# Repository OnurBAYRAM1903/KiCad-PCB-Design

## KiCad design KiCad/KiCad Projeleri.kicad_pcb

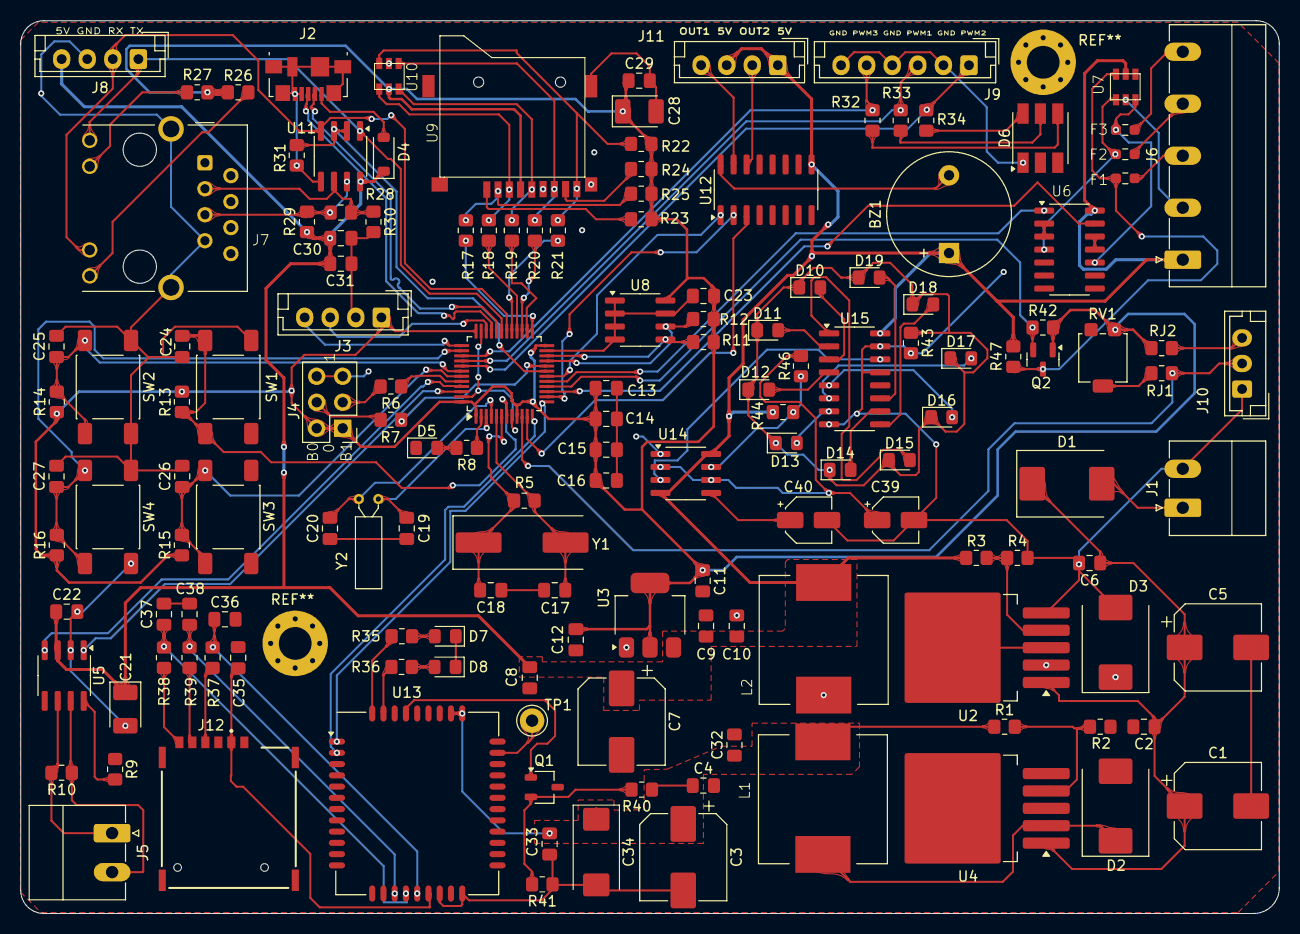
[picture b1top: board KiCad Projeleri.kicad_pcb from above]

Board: 2 copper layers, 123.0 x 87.2 mm, 149 parts (0 on the bottom side), 112 nets.

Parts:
BZ1: Buzzer; Buzzer_12x9.5RM7.6
C1, C5: 100uF-50V; CP_Elec_8x10
C2, C4, C6, C8, C10, C11, C13, C14, C15, C16, C22, C23, C24, C25, C26, C27, C30, C32, C33, C35: 100nF; C_0805_2012Metric_Pad1.18x1.45mm_HandSolder
C3, C7: 220uF-16V; CP_Elec_8x10
C9: 22uF; C_0805_2012Metric_Pad1.18x1.45mm_HandSolder
C12: 47uF; C_0805_2012Metric_Pad1.18x1.45mm_HandSolder
C17, C18, C19, C20: 22pF; C_0805_2012Metric_Pad1.18x1.45mm_HandSolder
C21: 47uF; CP_EIA-3528-21_Kemet-B_HandSolder
C28: 4.7uF-10V; CP_EIA-3528-21_Kemet-B_HandSolder
C29: 100nF-10V; C_0805_2012Metric_Pad1.18x1.45mm_HandSolder
C31: 10uF; C_0805_2012Metric_Pad1.18x1.45mm_HandSolder
C34: 100uF-10V; CP_EIA-7343-31_Kemet-D_HandSolder
C36, C37, C38: 33pF; C_0805_2012Metric_Pad1.18x1.45mm_HandSolder
C39: C_Polarized_Small; CP_Elec_4x5.4
C40: 1uF; CP_Elec_4x5.4
D1, D2, D3: SS34; D_SMC
D4: D_Schottky_Small; D_SOD-123
D5, D10, D11, D12, D13, D14, D15, D16, D17, D18, D19: LED_BLUE; LED_0805_2012Metric_Pad1.15x1.40mm_HandSolder
D6: LED_RGB; LED_RGB_5050-6
D7, D8: LED_ORANGE; LED_0805_2012Metric_Pad1.15x1.40mm_HandSolder
F1, F2, F3: RESETTABLE_FUSE-0603
J1: Conn_01x02; PhoenixContact_MC_1,5_2-G-3.81_1x02_P3.81mm_Horizontal
J2: USB_OTG; USB_Micro-B_Molex_47346-0001
J3, J8, J11: Conn_01x04; JST_EH_B4B-EH-A_1x04_P2.50mm_Vertical
J4: Conn_02x03_Counter_Clockwise; PinHeader_2x03_P2.54mm_Vertical
J5: Screw_Terminal_01x02; PhoenixContact_MC_1,5_2-G-3.81_1x02_P3.81mm_Horizontal
J6: Conn_01x05; PhoenixContact_MC_1,5_5-G-5.08_1x05_P5.08mm_Horizontal
J7: RJ45_USER
J9: Conn_01x06; JST_EH_B6B-EH-A_1x06_P2.50mm_Vertical
J10: Conn_01x03; JST_EH_B3B-EH-A_1x03_P2.50mm_Vertical
J12: SIM_Card-8066; GCT_SIM8066-6-1-14-01-A_REVA
L1, L2: 47uH; INDUCTOR_12x12x8
Q1: BC337; TSOT-23
Q2: BSS138; SOT-23
R1: 2K; R_0805_2012Metric_Pad1.20x1.40mm_HandSolder
R2, R4, R9, R26, R27, R28, R44, R46: 1K; R_0805_2012Metric_Pad1.20x1.40mm_HandSolder
R3: 3K; R_0805_2012Metric_Pad1.20x1.40mm_HandSolder
R5: 1M; R_0805_2012Metric_Pad1.20x1.40mm_HandSolder
R6, R7, R22, R31, R42, R47: 10K; R_0805_2012Metric_Pad1.20x1.40mm_HandSolder
R8, R33, R43: 330R; R_0805_2012Metric_Pad1.20x1.40mm_HandSolder
R10: 120R; R_0805_2012Metric_Pad1.20x1.40mm_HandSolder
R11, R12, R13, R14, R15, R16, R23, R24, R40, R41: 4K7; R_0805_2012Metric_Pad1.20x1.40mm_HandSolder
R17: 0R; R_0805_2012Metric_Pad1.20x1.40mm_HandSolder
R18, R19, R20, R37, R38, R39: 47R; R_0805_2012Metric_Pad1.20x1.40mm_HandSolder
R21: 1K8; R_0805_2012Metric_Pad1.20x1.40mm_HandSolder
R25: 47K; R_0805_2012Metric_Pad1.20x1.40mm_HandSolder
R29, R30: 20K; R_0805_2012Metric_Pad1.20x1.40mm_HandSolder
R32: 270R; R_0805_2012Metric_Pad1.20x1.40mm_HandSolder
R34: 590R; R_0805_2012Metric_Pad1.20x1.40mm_HandSolder
R35, R36: 470R; R_0805_2012Metric_Pad1.20x1.40mm_HandSolder
RJ1, RJ2: 0R; R_0805_2012Metric_Pad1.20x1.40mm_HandSolder
RV1: R_Potentiometer_US; Potentiometer_Bourns_3314G_Vertical
SW1, SW2, SW3, SW4: SW_Push; SW_Push_1P1T_NO_E-Switch_TL3301NxxxxxG
TP1: ANT; Pin_D1.0mm_L10.0mm_LooseFit
U1: STM32F103C8Tx; LQFP-48_7x7mm_P0.5mm
U2, U4: LM2596S-ADJ; TO-263-5_TabPin3
U3: AMS1117-3.3; SOT-223-3_TabPin2
U5: TJA1051T; SOIC-8_3.9x4.9mm_P1.27mm
U6: 74HC14_
U7, U10: TVS_5V
U8: M24C02-FMN; SOIC-8_3.9x4.9mm_P1.27mm
U9: SDCARD_KLS; L-KLS1-TF-003-SDCARD
U11: MAX485E; SOIC-8_3.9x4.9mm_P1.27mm
U12: ULN2003A; SOIC-16_3.9x9.9mm_P1.27mm
U13: SIM800C; SIMCom_SIM800C
U14: NE555D; SOIC-8_3.9x4.9mm_P1.27mm
U15: 4017; SOP-16_3.9x9.9mm_P1.27mm
Y1: Crystal_Small; Crystal_SMD_HC49-SD
Y2: Crystal_Small; Crystal_C26-LF_D2.1mm_L6.5mm_Horizontal

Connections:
3V3: C11.1, C12.1, C13.1, C14.1, C15.1, C16.1, C23.1, C28.1, C29.1, J3.1, J4.1, J4.2, Q2.1 (G), R11.1, R12.1, R13.1, R14.1, R15.1, R16.1, R22.2, R23.2, R24.2, R25.2, R26.1, R27.1, R42.2, RJ2.2, RV1.1, U1.1 (VBAT), U1.9 (VDDA), U1.24 (VDD), U1.36 (VDD), U1.48 (VDD), U3.2 (VO), U8.8 (VCC), U9.4 (VDD), U10.5 (VCC)
3V7: C3.1, C4.1, C32.1, C33.1, C34.1, L1.2, R1.1, R40.2, U13.34 (VBAT), U13.35 (VBAT)
5V: BZ1.1 (+), C7.1, C8.1, C9.1, C10.1, C21.1, C22.1, C30.1, C31.1, D4.1 (K), J6.1, J8.4, J11.1, J11.3, L2.2, R3.1, R29.1, R44.2, R47.2, U3.3 (VI), U5.3 (VCC), U6.14 (VCC), U7.5 (VCC), U11.8 (VCC), U12.9 (COM), U14.4 (R), U14.8 (VCC), U15.16 (VDD)
ADC1: J10.2, RJ1.2, U1.10 (PA0)
BOOT0: R6.1, U1.44 (BOOT0)
BOOT1: R7.2, U1.20 (PB2)
BUZZER: U1.18 (PB0), U12.1 (I1)
CAN_RX: U1.45 (PB8), U5.4 (RXD)
CAN_TX: U1.46 (PB9), U5.1 (TXD)
CLK_SIM: C37.1, R38.2, U13.16 (SIM_CLK)
DATA_SIM: C38.1, R39.2, U13.15 (SIM_DATA)
D_N: J2.2 (D-), U1.32 (PA11)
D_P: J2.3 (D+), U1.33 (PA12)
EXTI6: C25.1, R14.2, SW2.1, U1.42 (PB6)
EXTI7: C26.1, R15.2, SW3.1, U1.43 (PB7)
EXTI15: C27.1, R16.2, SW4.1, U1.38 (PA15)
GND: C1.2, C2.2, C3.2, C4.2, C5.2, C6.2, C7.2, C8.2, C9.2, C10.2, C11.2, C12.2, C13.2, C14.2, C15.2, C16.2, C17.1, C18.1, C19.1, C20.1, C21.2, C22.2, C23.2, C24.2, C25.2, C26.2, C27.2, C28.2, C29.2, C30.2, C31.2, C32.2, C33.2, C34.2, C35.2, C36.2, C37.2, C38.2, C39.2, C40.2, D2.2 (A), D3.2 (A), D5.1 (K), D6.1 (RK), D6.2 (GK), D6.3 (BK), D7.1 (K), D8.1 (K), J1.2, J2.4 (ID), J2.5 (GND), J2.6 (Shield), J3.2, J4.5, J4.6, J6.2, J7.7, J7.SH, J8.3, J9.2, J9.4, J9.6, J10.1, J12.5 (GND), Q1.3 (E), R2.2, R4.2, R9.1, R30.2, R31.2, R41.2, R43.2, RV1.3, SW1.2, SW2.2, SW3.2, SW4.2, U1.8 (VSSA), U1.23 (VSS), U1.35 (VSS), U1.47 (VSS), U2.3 (GND), U2.5 (~ON/OFF), U3.1 (GND), U4.3 (GND), U4.5 (~ON/OFF), U5.2 (GND), U6.7 (GND), U7.2 (GND), U8.1 (E0), U8.2 (E1), U8.3 (E2), U8.4 (VSS), U8.7 (~WC), U9.6 (VSS), U9.10 (GND), U9.11 (SHIELD), U10.2 (GND), U11.5 (GND), U12.8 (GND), U13.8 (GND), U13.13 (GND), U13.19 (GND), U13.21 (GND), U13.27 (GND), U13.30 (GND), U13.31 (GND), U13.33 (GND), U13.36 (GND), U13.37 (GND), U14.1 (GND), U15.8 (VSS), U15.13 (CKEN), U15.15 (Reset)
HSE_OSC_IN: C17.2, R5.1, U1.5 (PD0), Y1.2
HSE_OSC_OUT: C18.2, R5.2, U1.6 (PD1), Y1.1
I2C_EEPROM_SCL: R12.2, U1.21 (PB10), U8.6 (SCL)
I2C_EEPROM_SDA: R11.2, U1.22 (PB11), U8.5 (SDA)
LSE_OSC_IN: C19.2, U1.3 (PC14), Y2.2
LSE_OSC_OUT: C20.2, U1.4 (PC15), Y2.1
MISO: F1.1, Q2.3 (D), R47.1, U7.6 (IO2)
MOSI_: F2.1, U6.4 (2Y), U7.1 (IO1)
unnamed: BZ1.2 (-), U12.16 (O1)
unnamed: D1.2 (A), J1.1
unnamed: D2.1 (K), L1.1, U4.2 (OUT)
unnamed: D3.1 (K), L2.1, U2.2 (OUT)
unnamed: D4.2 (A), J2.1 (VBUS)
unnamed: D5.2 (A), R8.2
unnamed: D6.4 (BA), R32.2
unnamed: D6.5 (GA), R33.2
unnamed: D6.6 (RA), R34.2
unnamed: D7.2 (A), R35.1
unnamed: D8.2 (A), R36.2
unnamed: D10.2 (A), U15.3 (Q0)
unnamed: D10.1 (K), D11.1 (K), D12.1 (K), D13.1 (K), D14.1 (K), D15.1 (K), D16.1 (K), D17.1 (K), D18.1 (K), D19.1 (K), R43.1
unnamed: D11.2 (A), U15.2 (Q1)
unnamed: D12.2 (A), U15.4 (Q2)
unnamed: D13.2 (A), U15.7 (Q3)
unnamed: D14.2 (A), U15.10 (Q4)
unnamed: D15.2 (A), U15.1 (Q5)
unnamed: D16.2 (A), U15.5 (Q6)
unnamed: D17.2 (A), U15.6 (Q7)
unnamed: D18.2 (A), U15.9 (Q8)
unnamed: D19.2 (A), U15.11 (Q9)
unnamed: J4.3, R6.2
unnamed: J4.4, R7.1
unnamed: J5.1, R10.2, U5.6 (CANL)
unnamed: J5.2, R10.1, U5.7 (CANH)
unnamed: F1.2, J6.3
unnamed: F2.2, J6.4
unnamed: F3.2, J6.5
unnamed: J7.10, R27.2
unnamed: J7.12, R26.2
unnamed: J10.3, RJ2.1
unnamed: J11.2, U12.14 (O3)
unnamed: J11.4, U12.15 (O2)
unnamed: J12.3 (CLK), R38.1
unnamed: J12.7 (I/O), R39.1
unnamed: J12.2 (RST), R37.1
unnamed: Q1.2 (B), R40.1, R41.1
unnamed: RJ1.1, RV1.2
unnamed: R3.2, R4.1, U2.4 (FB)
unnamed: R1.2, R2.1, U4.4 (FB)
unnamed: R9.2, U5.8 (S)
unnamed: U6.2 (1Y), U6.3 (2A)
unnamed: U6.11 (5A), U6.12 (6Y)
unnamed: R17.2, R25.1, U9.2 (CS)
unnamed: R24.1, U9.8 (DAT1)
unnamed: R23.1, U9.1 (DAT2)
unnamed: R20.2, U9.7 (MISO/DAT0), U10.1 (IO1)
unnamed: R19.2, U9.5 (CLK), U10.6 (IO2)
unnamed: R21.2, R22.1, U9.9 (DETECT_SDCARD), U10.3 (IO3)
unnamed: R18.2, U9.3 (MOSI/CMD), U10.4 (IO4)
unnamed: J7.3, R28.2, R30.1, U11.6 (A)
unnamed: J7.5, R28.1, R29.2, U11.7 (B)
unnamed: TP1.1, U13.32 (GSM_ANT)
unnamed: R36.1, U13.41 (NETLIGHT)
unnamed: R35.2, U13.42 (STATUS)
unnamed: C40.1, U14.5 (CV)
unnamed: R44.1, R46.2, U14.7 (DIS)
unnamed: U14.3 (Q), U15.14 (CLK)
unnamed: C39.1, R46.1, U14.2 (TR), U14.6 (THR)
OUT1: U1.14 (PA4), U12.2 (I2)
OUT2: U1.11 (PA1), U12.3 (I3)
PC13_LED: R8.1, U1.2 (PC13)
PWM1: J9.3, R33.1, U1.40 (PB4)
PWM2: J9.1, R34.1, U1.41 (PB5)
PWM3: J9.5, R32.1, U1.39 (PB3)
PWRKEY: Q1.1 (C), U13.39 (~PWRKEY)
RESET: C24.1, R13.2, SW1.1, U1.7 (NRST)
RESET_SIM: C36.1, R37.2, U13.17 (SIM_RST)
RS485_TX_RX_END: R31.1, U1.19 (PB1), U11.2 (~RE), U11.3 (DE)
SCLK: F3.1, U6.10 (5Y), U7.3 (IO3)
SPI1_MISO: Q2.2 (S), R42.1, U1.16 (PA6)
SPI1_MOSI: U1.17 (PA7), U6.1 (1A)
SPI1_SCK: U1.15 (PA5), U6.13 (6A)
SPI_SD_DETECT: R21.1, U1.29 (PA8)
SPI_SD_MISO: R20.1, U1.27 (PB14)
SPI_SD_MOSI: R18.1, U1.28 (PB15)
SPI_SD_NSS: R17.1, U1.25 (PB12)
SPI_SD_SCK: R19.1, U1.26 (PB13)
SWCLK: J3.4, U1.37 (PA14)
SWDIO: J3.3, U1.34 (PA13)
UART2_SIM800C_RX: U1.13 (PA3), U13.1 (UART1_TXD)
UART2_SIM800C_TX: U1.12 (PA2), U13.2 (UART1_RXD)
USART1_FTDI_RX_RS_485_TX: J7.9, J8.1, U1.31 (PA10), U11.1 (RO)
USART1_FTDI_TX_RS_485_RX: J7.11, J8.2, U1.30 (PA9), U11.4 (DI)
VDD_SIM: C35.1, J12.1 (VCC), U13.18 (SIM_VDD)
VIN: C1.1, C2.1, C5.1, C6.1, D1.1 (K), U2.1 (VIN), U4.1 (VIN)

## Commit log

2025-07-24 First
2025-07-24 Second
2025-07-24 Last
